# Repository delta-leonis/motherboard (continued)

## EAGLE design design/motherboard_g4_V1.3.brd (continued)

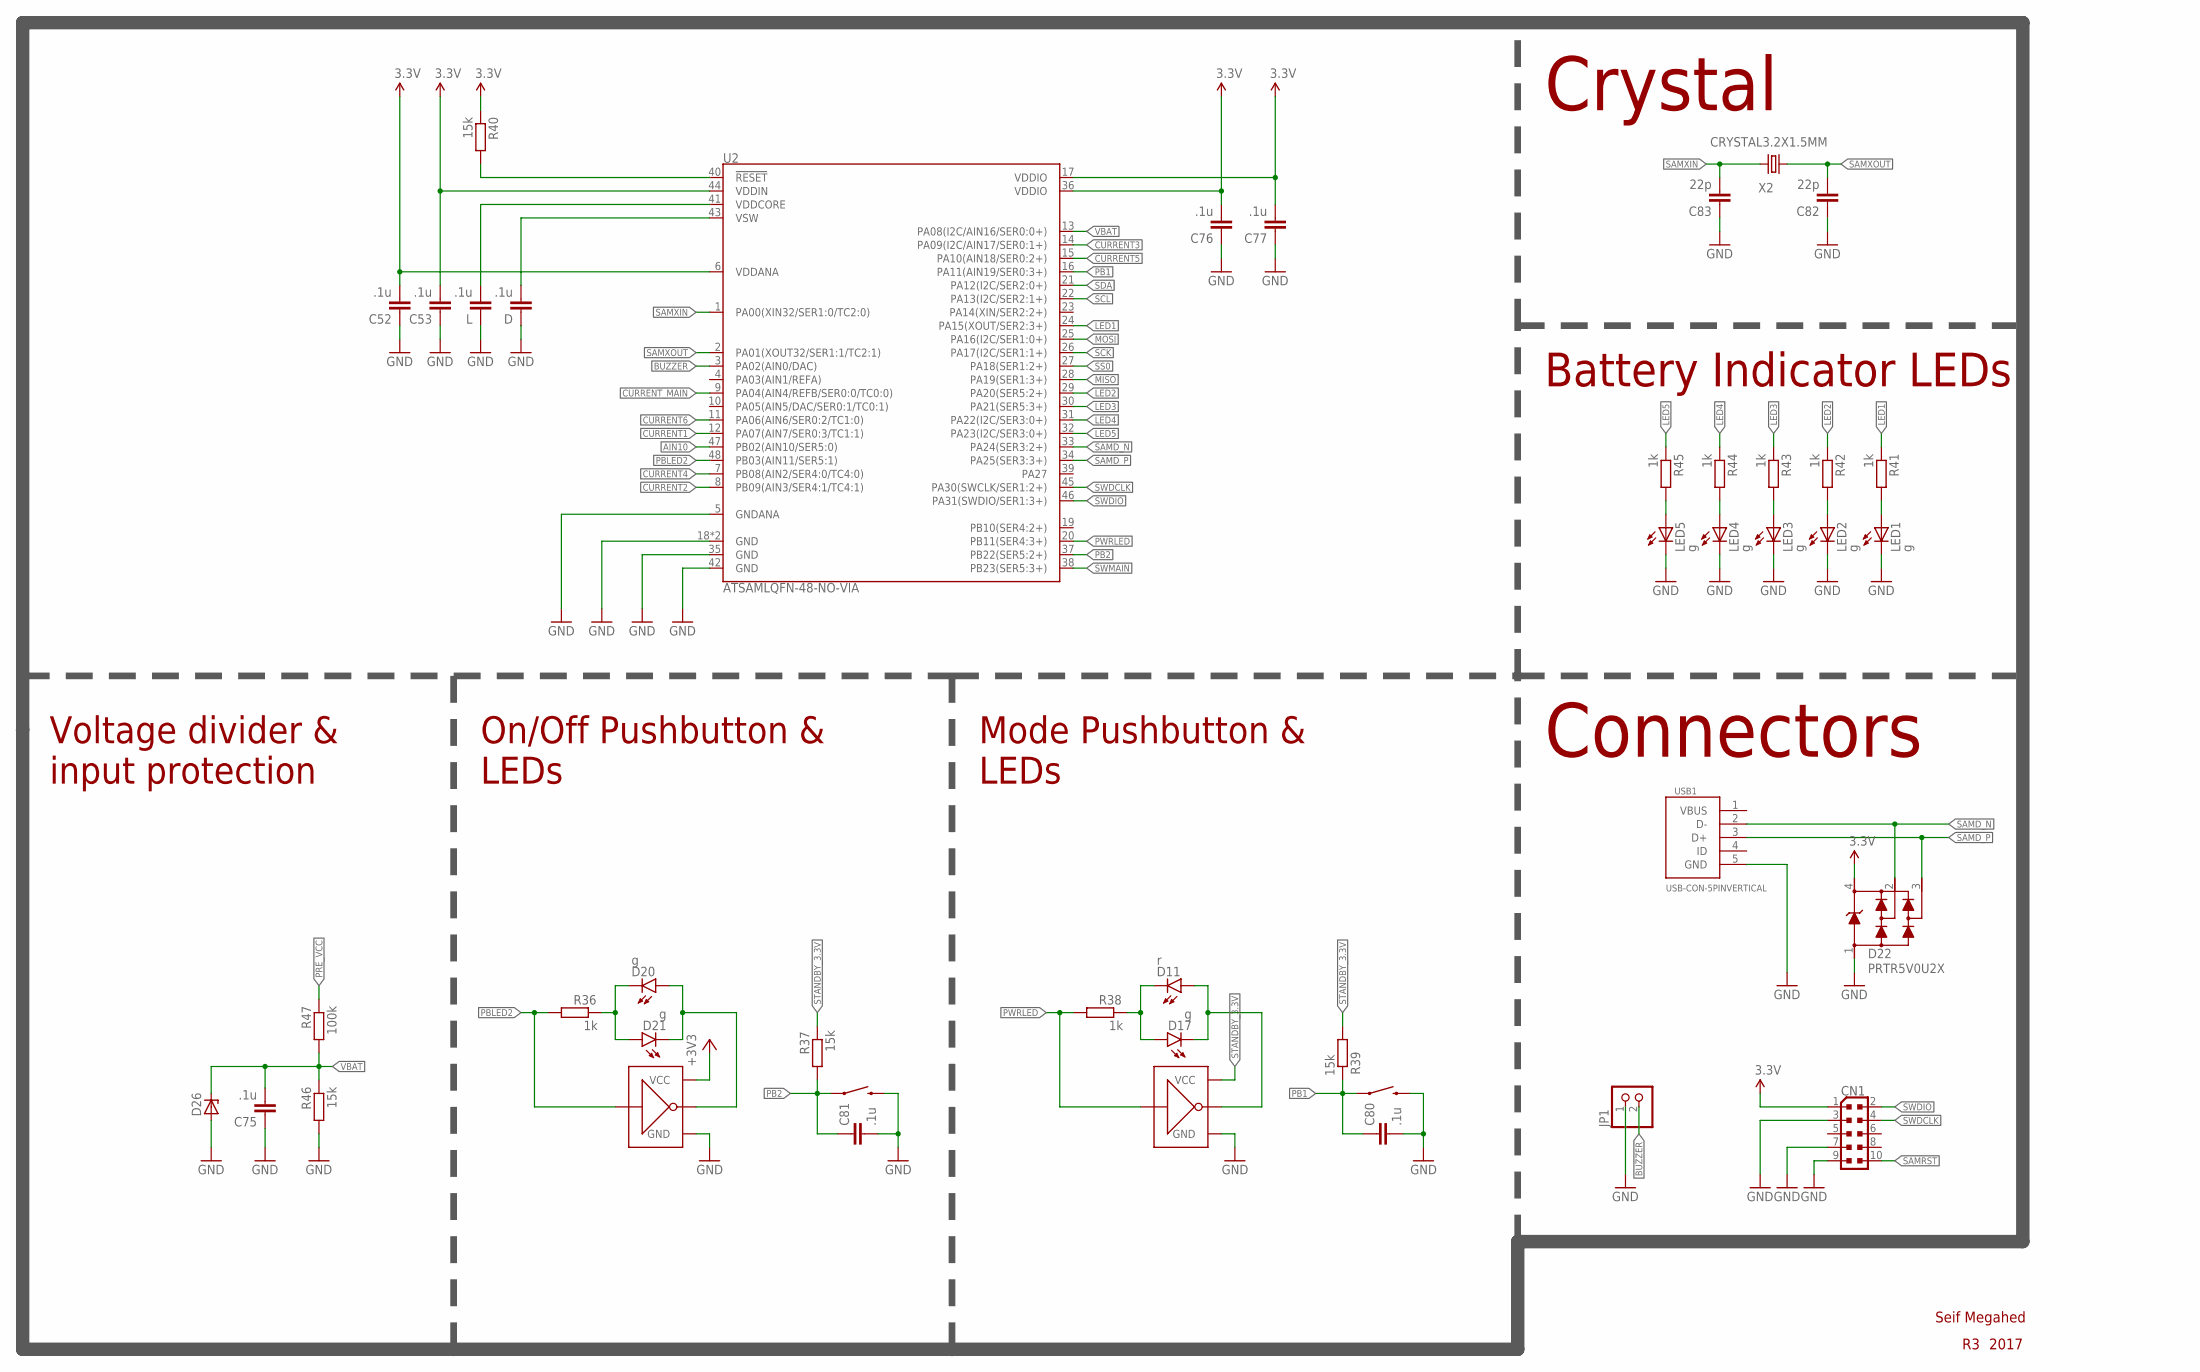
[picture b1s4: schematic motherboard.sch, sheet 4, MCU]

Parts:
C52, C53, C75, C76, C77, C80, C81: .1u; CAP_0603
C82, C83: 22p; CAP_0603
CN1: SWD_0171_PH127-205DF055G00AROUND-PADS; SWD_PINHEAD_2X05_127
D: .1u; CAP_0603
D11: r; LED-0603
D17, D20, D21: g; LED-0603
D22: PRTR5V0U2X; SOT143B
D26: http://nl.farnell.com/diodes-inc/dz23c3v3-7-f/dio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; SOT23
JP1: PINHD-1X2; 1X02
L: .1u; CAP_0603
LED1, LED2, LED3, LED4, LED5: g; CHIP-LED0603
NOT1, NOT2: NOT_GATE7404_SOT23-5; SOT23-5
R36, R38: 1k; 0603
R37, R39: 15k; 0603
R40, R46: 15k; RES_0603
R41, R42, R43, R44, R45: 1k; RES_0603
R47: 100k; RES_0603
U2: ATSAMLQFN-48-NO-VIA; QFN-48-NO-VIAS
U$31, U$32: http://nl.mouser.com/ProductDetail/Omron-Electron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; TACT12X12
USB1: USB-CON-5PINVERTICAL; USB-MICRO-3131-V
X2: CRYSTAL3.2X1.5MM; CRYSTAL-SMD-3.2X1.5MM

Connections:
+3V3: NOT2.5 (VCC); also elsewhere on the board
AIN10: U2.47 (PB02(AIN10/SER5:0))
BUZZER: JP1.2, U2.3 (PA02(AIN0/DAC))
CURRENT1: U2.12 (PA07(AIN7/SER0:3/TC1:1)); also elsewhere on the board
CURRENT2: U2.8 (PB09(AIN3/SER4:1/TC4:1)); also elsewhere on the board
CURRENT3: U2.14 (PA09(I2C/AIN17/SER0:1+)); also elsewhere on the board
CURRENT4: U2.7 (PB08(AIN2/SER4:0/TC4:0)); also elsewhere on the board
CURRENT5: U2.15 (PA10(AIN18/SER0:2+)); also elsewhere on the board
CURRENT6: U2.11 (PA06(AIN6/SER0:2/TC1:0)); also elsewhere on the board
CURRENT_MAIN: U2.9 (PA04(AIN4/REFB/SER0:0/TC0:0)); also elsewhere on the board
D: D.2, U2.43 (VSW)
GND: C52.1, C53.1, C75.1, C76.1, C77.1, C80.2, C81.2, C82.1, C83.1, CN1.3, CN1.7, CN1.9, D.1, D22.1, D26.1 (A), JP1.1, L.1, LED1.C, LED2.C, LED3.C, LED4.C, LED5.C, NOT1.3 (GND), NOT2.3 (GND), R46.2, U2.5 (GNDANA), U2.18 (GND), U2.35 (GND), U2.42 (GND), U2.EP (GND), U$31.3 (2), U$31.4 (2), U$32.3 (2), U$32.4 (2), USB1.5 (GND); also elsewhere on the board
L: L.2, U2.41 (VDDCORE)
LED1: R41.1, U2.24 (PA15(XOUT/SER2:3+))
LED2: R42.1, U2.29 (PA20(SER5:2+))
LED3: R43.1, U2.30 (PA21(SER5:3+))
LED4: R44.1, U2.31 (PA22(I2C/SER3:0+))
LED5: R45.1, U2.32 (PA23(I2C/SER3:0+))
MISO: U2.28 (PA19(SER1:3+)); also elsewhere on the board
MOSI: U2.25 (PA16(I2C/SER1:0+)); also elsewhere on the board
unnamed: D20.C, D21.A, R36.P$1 (1)
unnamed: D11.C, D17.A, R38.P$1 (1)
unnamed: D11.A, D17.C, NOT1.4 (Y)
unnamed: D20.A, D21.C, NOT2.4 (Y)
unnamed: LED5.A, R45.2
unnamed: LED4.A, R44.2
unnamed: LED3.A, R43.2
unnamed: LED2.A, R42.2
unnamed: LED1.A, R41.2
PB1: C80.1, R39.P$1 (1), U2.16 (PA11(AIN19/SER0:3+)), U$31.1, U$31.2 (1)
PB2: C81.1, R37.P$2 (2), U2.37 (PB22(SER5:2+)), U$32.1, U$32.2 (1)
PBLED2: NOT2.2 (A), R36.P$2 (2), U2.48 (PB03(AIN11/SER5:1))
PRE_VCC: R47.1; also elsewhere on the board
PWRLED: NOT1.2 (A), R38.P$2 (2), U2.20 (PB11(SER4:3+))
SAMD_N: D22.2, U2.33 (PA24(SER3:2+)), USB1.2 (D-)
SAMD_P: D22.3, U2.34 (PA25(SER3:3+)), USB1.3 (D+)
SAMRST: CN1.10, R40.2, U2.40 (!RESET!)
SAMXIN: C83.2, U2.1 (PA00(XIN32/SER1:0/TC2:0)), X2.P$2 (2)
SAMXOUT: C82.2, U2.2 (PA01(XOUT32/SER1:1/TC2:1)), X2.P$1 (1)
SCK: U2.26 (PA17(I2C/SER1:1+)); also elsewhere on the board
SCL: U2.22 (PA13(I2C/SER2:1+)); also elsewhere on the board
SDA: U2.21 (PA12(I2C/SER2:0+)); also elsewhere on the board
SS0: U2.27 (PA18(SER1:2+)); also elsewhere on the board
STANDBY_3.3V: C52.2, C53.2, C76.2, C77.2, CN1.1, D22.4, NOT1.5 (VCC), R37.P$1 (1), R39.P$2 (2), R40.1, U2.6 (VDDANA), U2.17 (VDDIO), U2.36 (VDDIO), U2.44 (VDDIN); also elsewhere on the board
SWDCLK: CN1.4, U2.45 (PA30(SWCLK/SER1:2+))
SWDIO: CN1.2, U2.46 (PA31(SWDIO/SER1:3+))
SWMAIN: U2.38 (PB23(SER5:3+)); also elsewhere on the board
VBAT: C75.2, D26.3 (C), R46.1, R47.2, U2.13 (PA08(I2C/AIN16/SER0:0+))
VBUS: USB1.1 (VBUS)

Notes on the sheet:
Connectors
Battery Indicator LEDs
Crystal
Voltage divider & input protection
On/Off Pushbutton & LEDs
Mode Pushbutton & LEDs
Seif Megahed
2017

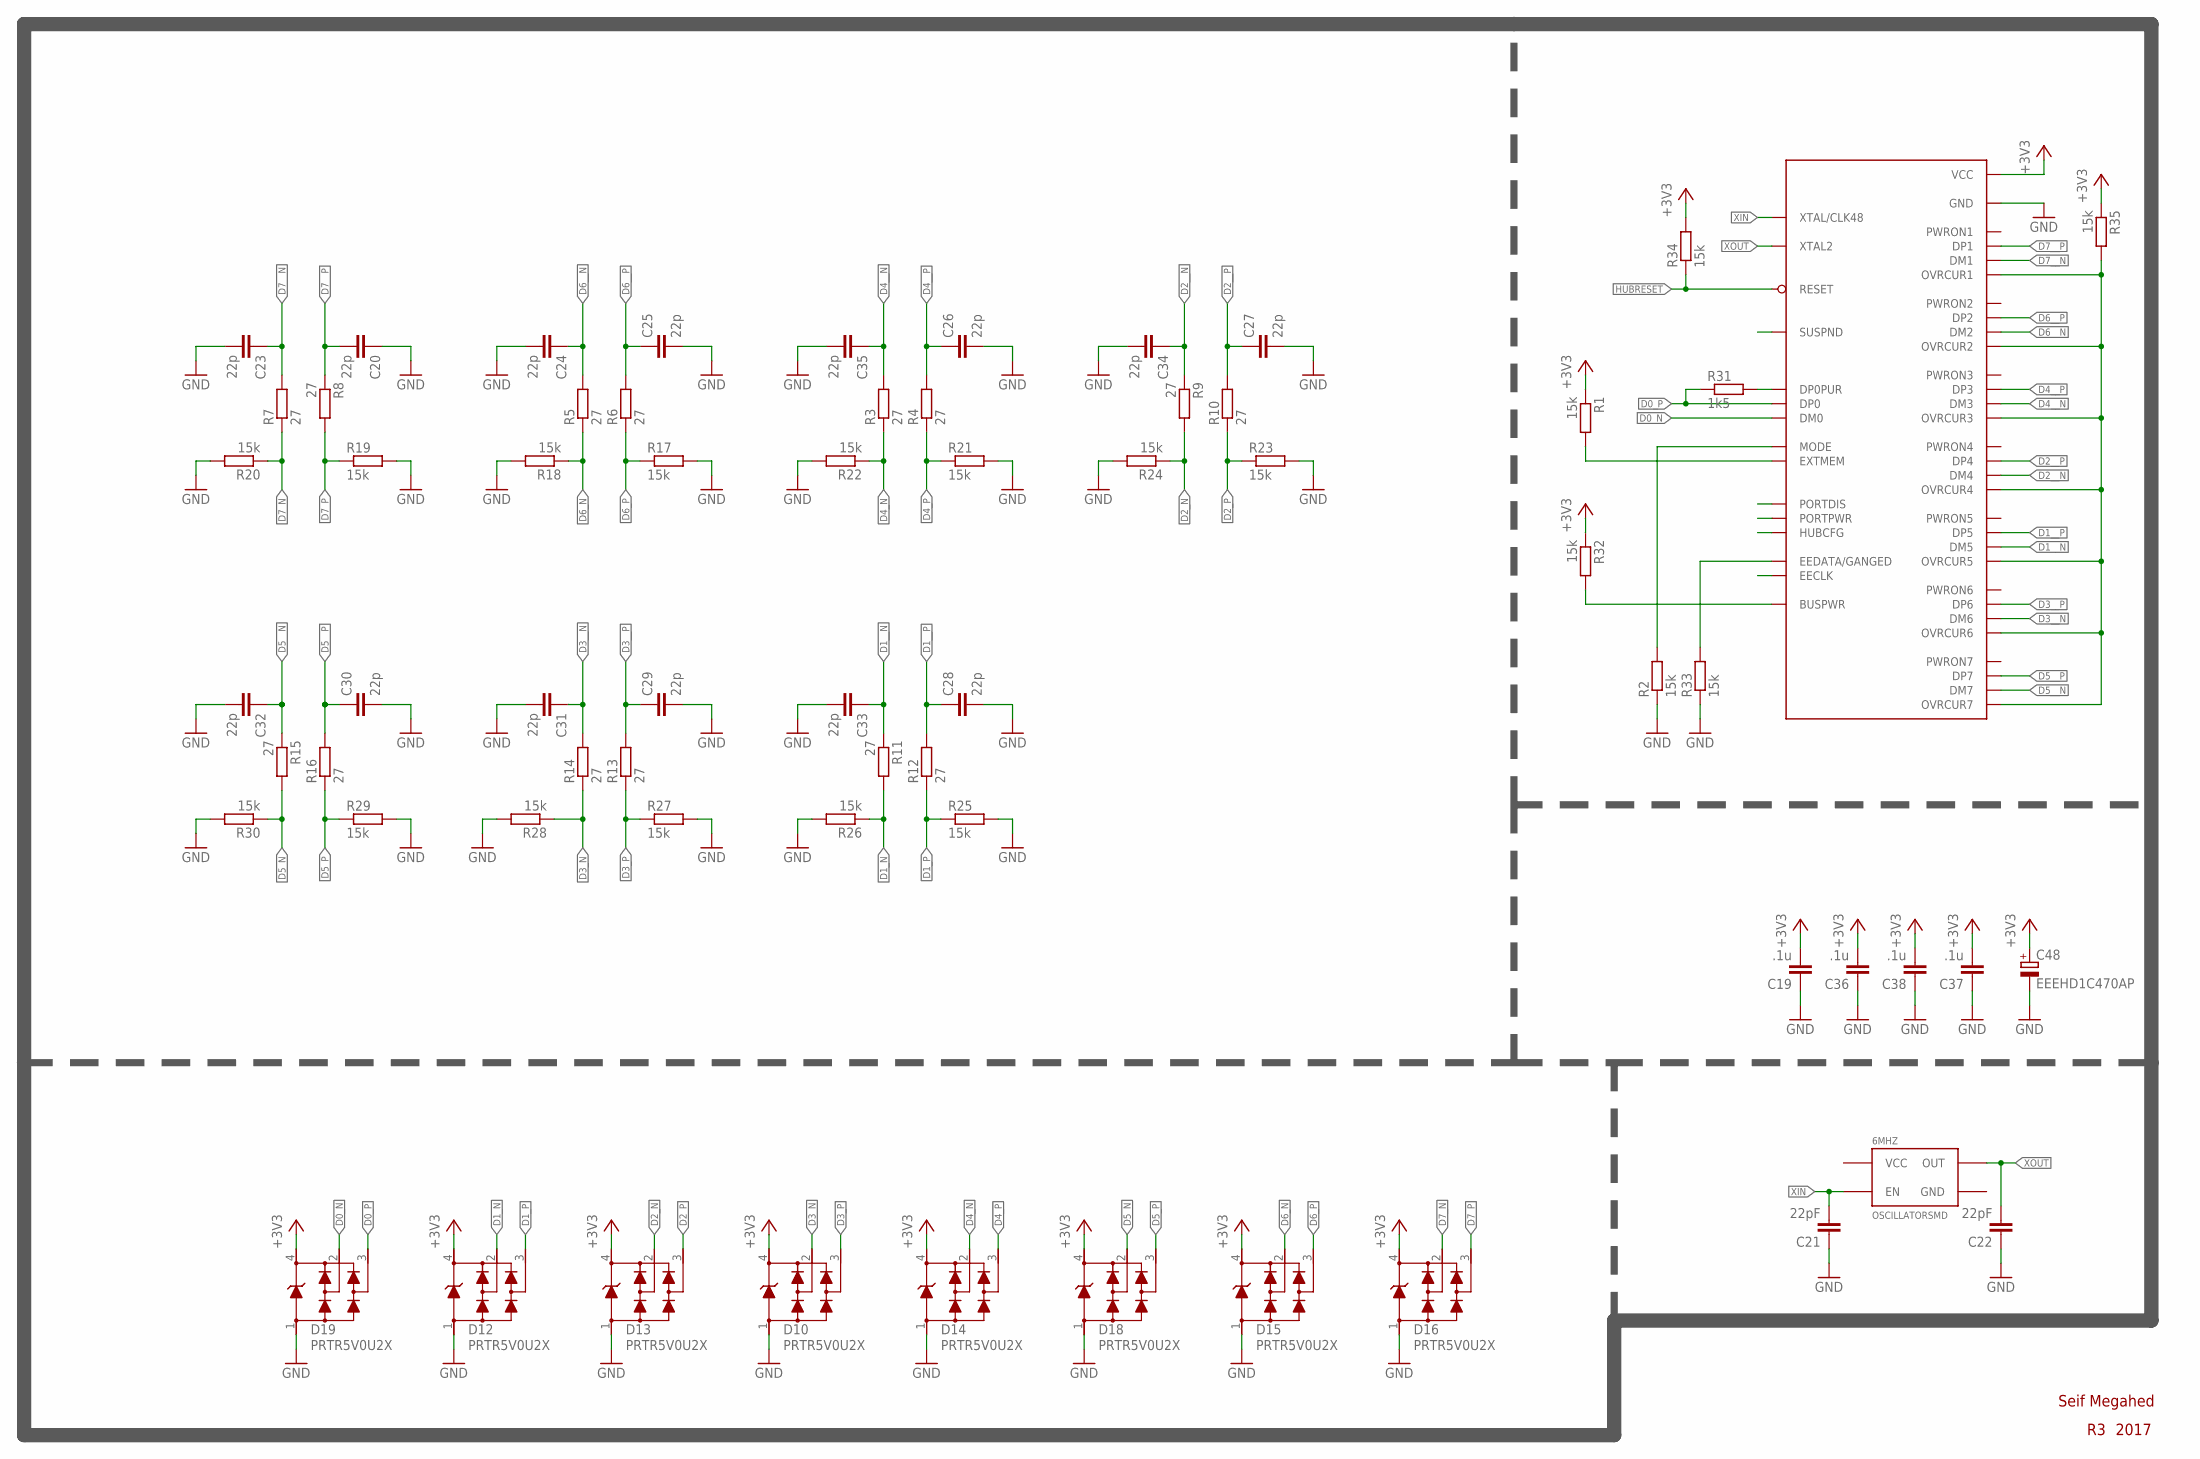
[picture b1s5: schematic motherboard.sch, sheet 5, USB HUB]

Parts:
6MHZ: OSCILLATORSMD; CRYSTAL-SMD-7X5
C19, C36, C37, C38: .1u; CAP_0603
C20, C23, C24, C25, C26, C27, C28, C29, C30, C31, C32, C33, C34, C35: 22p; CAP_0603
C21, C22: 22pF; CAP_0603
C48: EEEHD1C470AP; PANASONIC_C
D10, D12, D13, D14, D15, D16, D18, D19: PRTR5V0U2X; SOT143B
R1, R2, R17, R18, R19, R20, R21, R22, R23, R24, R25, R26, R27, R28, R29, R30, R32, R33, R34, R35: 15k; RES_0603
R3, R4, R5, R6, R7, R8, R9, R10, R11, R12, R13, R14, R15, R16: 27; RES_0603
R31: 1k5; RES_0603
U1: TUSB2077ALQFP-48; LQFP-48

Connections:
+3V3: C19.2, C36.2, C37.2, C38.2, C48.+, D10.4, D12.4, D13.4, D14.4, D15.4, D16.4, D18.4, D19.4, R1.1, R32.1, R34.2, R35.1, U1.9 (VCC), U1.46 (VCC); also elsewhere on the board
BUSPWR: R32.2, U1.10 (BUSPWR)
D0_N: D19.2, U1.4 (DM0); also elsewhere on the board
D0_P: D19.3, R31.1, U1.3 (DP0); also elsewhere on the board
D1_N: D12.2, R11.2, R26.1; also elsewhere on the board
D1_P: D12.3, R12.1, R25.1; also elsewhere on the board
D1__N: C33.1, R11.1, U1.30 (DM5)
D1__P: C28.1, R12.2, U1.31 (DP5)
D2_N: D13.2, R9.2, R24.1; also elsewhere on the board
D2_P: D13.3, R10.1, R23.1; also elsewhere on the board
D2__N: C34.1, R9.1, U1.26 (DM4)
D2__P: C27.1, R10.2, U1.27 (DP4)
D3_N: D10.2, R14.1, R28.1; also elsewhere on the board
D3_P: D10.3, R13.1, R27.1; also elsewhere on the board
D3__N: C31.1, R14.2, U1.34 (DM6)
D3__P: C29.1, R13.2, U1.35 (DP6)
D4_N: D14.2, R3.1, R22.1; also elsewhere on the board
D4_P: D14.3, R4.1, R21.1; also elsewhere on the board
D4__N: C35.1, R3.2, U1.21 (DM3)
D4__P: C26.1, R4.2, U1.22 (DP3)
D5_N: D18.2, R15.2, R30.1; also elsewhere on the board
D5_P: D18.3, R16.1, R29.1; also elsewhere on the board
D5__N: C32.1, R15.1, U1.38 (DM7)
D5__P: C30.1, R16.2, U1.39 (DP7)
D6_N: D15.2, R5.1, R18.1; also elsewhere on the board
D6_P: D15.3, R6.1, R17.1; also elsewhere on the board
D6__N: C24.1, R5.2, U1.17 (DM2)
D6__P: C25.1, R6.2, U1.18 (DP2)
D7_N: D16.2, R7.1, R20.1; also elsewhere on the board
D7_P: D16.3, R8.2, R19.1; also elsewhere on the board
D7__N: C23.1, R7.2, U1.13 (DM1)
D7__P: C20.2, R8.1, U1.14 (DP1)
DPUR: R31.2, U1.2 (DP0PUR)
EEDATA: R33.2, U1.8 (EEDATA/GANGED)
EXTMEM: R1.2, U1.47 (EXTMEM)
GND: C19.1, C20.1, C21.1, C22.1, C23.2, C24.2, C25.2, C26.2, C27.2, C28.2, C29.2, C30.2, C31.2, C32.2, C33.2, C34.2, C35.2, C36.1, C37.1, C38.1, C48.-, D10.1, D12.1, D13.1, D14.1, D15.1, D16.1, D18.1, D19.1, R2.1, R17.2, R18.2, R19.2, R20.2, R21.2, R22.2, R23.2, R24.2, R25.2, R26.2, R27.2, R28.2, R29.2, R30.2, R33.1, U1.5 (GND), U1.24 (GND), U1.43 (GND); also elsewhere on the board
HUBRESET: R34.1, U1.6 (RESET)
MODE: R2.2, U1.48 (MODE)
OC: R35.2, U1.12 (OVRCUR1), U1.16 (OVRCUR2), U1.20 (OVRCUR3), U1.25 (OVRCUR4), U1.29 (OVRCUR5), U1.33 (OVRCUR6), U1.37 (OVRCUR7)
XIN: 6MHZ.P$1 (EN), C21.2, U1.45 (XTAL/CLK48)
XOUT: 6MHZ.P$3 (OUT), C22.2, U1.44 (XTAL2)

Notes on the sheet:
Seif Megahed
2017

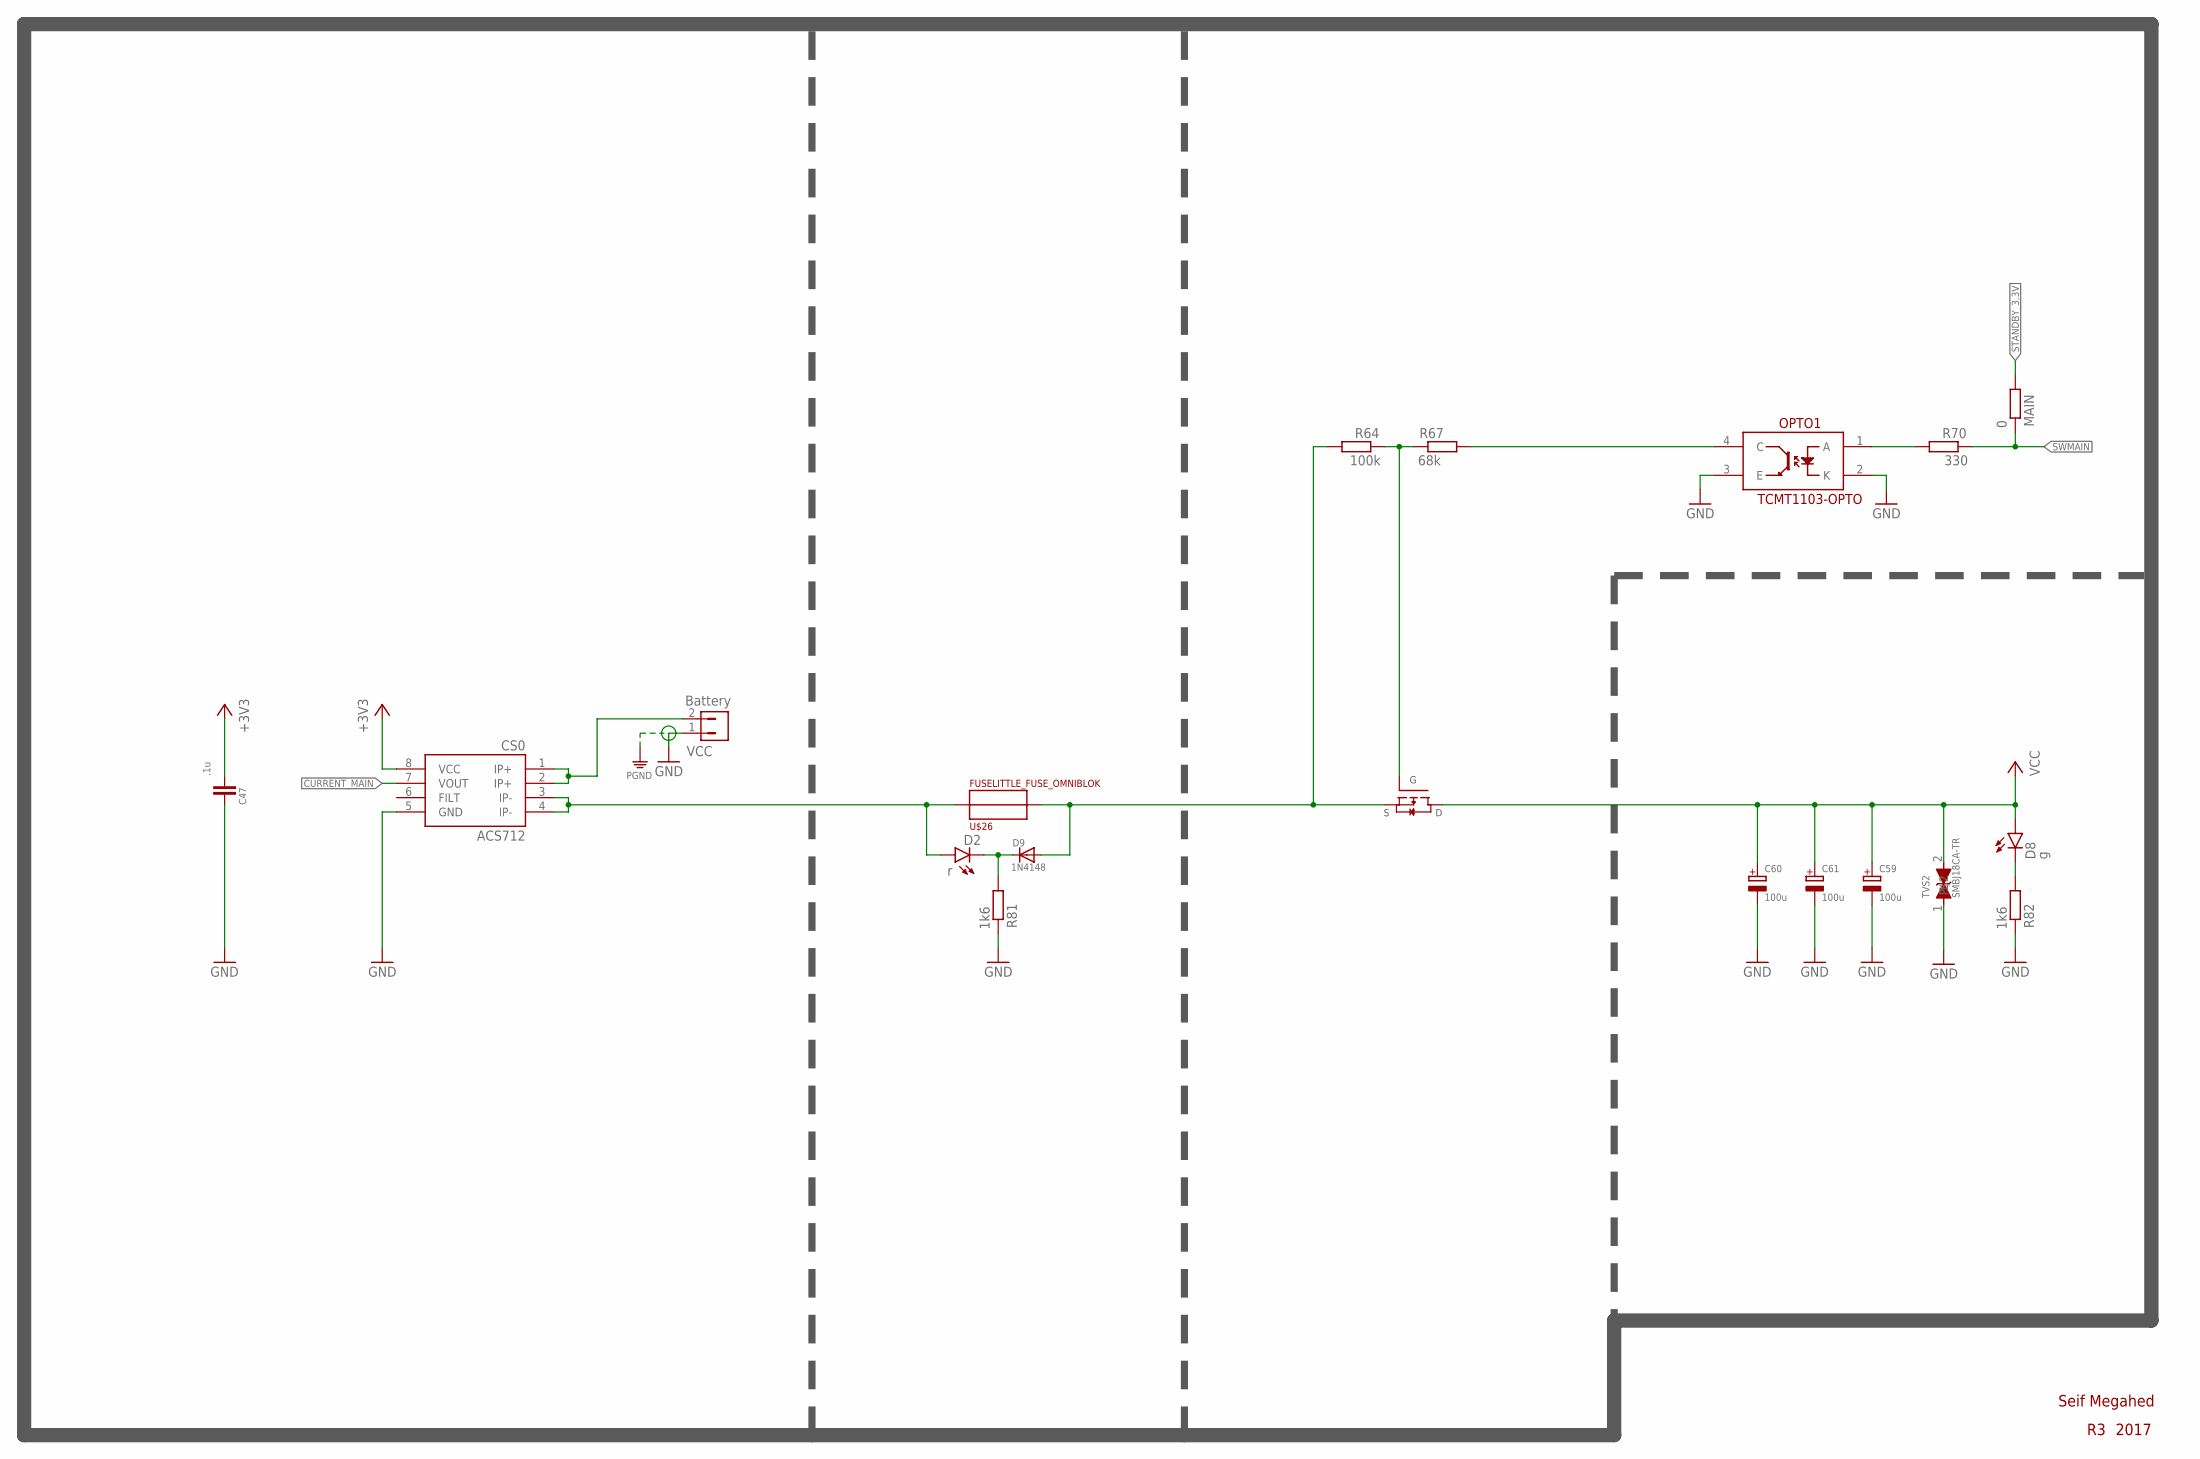
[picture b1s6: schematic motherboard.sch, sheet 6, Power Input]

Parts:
C47: .1u; 0603
C59, C60, C61: 100u; AE_CAP_D
CS0: ACS712; SO08
D2: r; LED-0603
D8: g; LED-0603
D9: 1N4148; SOD-80
MAIN: 0; 0603
OPTO1: TCMT1103-OPTO; SSOP-4
R64: 100k; 0603
R67: 68k; 0603
R70: 330; 0603
R81, R82: 1k6; 0603
TVS2: SMBJ18CA-TR; IPC_7531
U$26: FUSELITTLE_FUSE_OMNIBLOK; OMNI_BLOK
U$30: MOSFETSIR401DP; POWERPAK_SO-8
VCC: Battery; MOLEX_2_RIGHT

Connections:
+3V3: C47.P$2 (2), CS0.8 (VCC); also elsewhere on the board
BAT: CS0.1 (IP+), CS0.2 (IP+), VCC.2
CURRENT_MAIN: CS0.7 (VOUT); also elsewhere on the board
GND: C47.P$1 (1), C59.-, C60.-, C61.-, CS0.5 (GND), OPTO1.2 (K), OPTO1.3 (E), R81.P$1 (1), R82.P$1 (1), TVS2.1, VCC.1; also elsewhere on the board
MOSFET_GATE: OPTO1.4 (C), R67.P$2 (2)
unnamed: R64.P$1 (1), R67.P$1 (1), U$30.4 (G)
unnamed: OPTO1.1 (A), R70.P$2 (2)
unnamed: D2.C, D9.2 (C), R81.P$2 (2)
unnamed: D8.C, R82.P$2 (2)
PRE_VCC: CS0.3 (IP-), CS0.4 (IP-), D2.A, U$26.P$1; also elsewhere on the board
S: D9.1 (A), R64.P$2 (2), U$26.P$2, U$30.1 (S), U$30.2 (S), U$30.3 (S)
STANDBY_3.3V: MAIN.P$2 (2); also elsewhere on the board
SWMAIN: MAIN.P$1 (1), R70.P$1 (1); also elsewhere on the board
VCC: C59.+, C60.+, C61.+, D8.A, TVS2.2, U$30.5 (D), U$30.6 (D), U$30.7 (D), U$30.8 (D), U$30.EP (D); also elsewhere on the board

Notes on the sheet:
Seif Megahed
2017

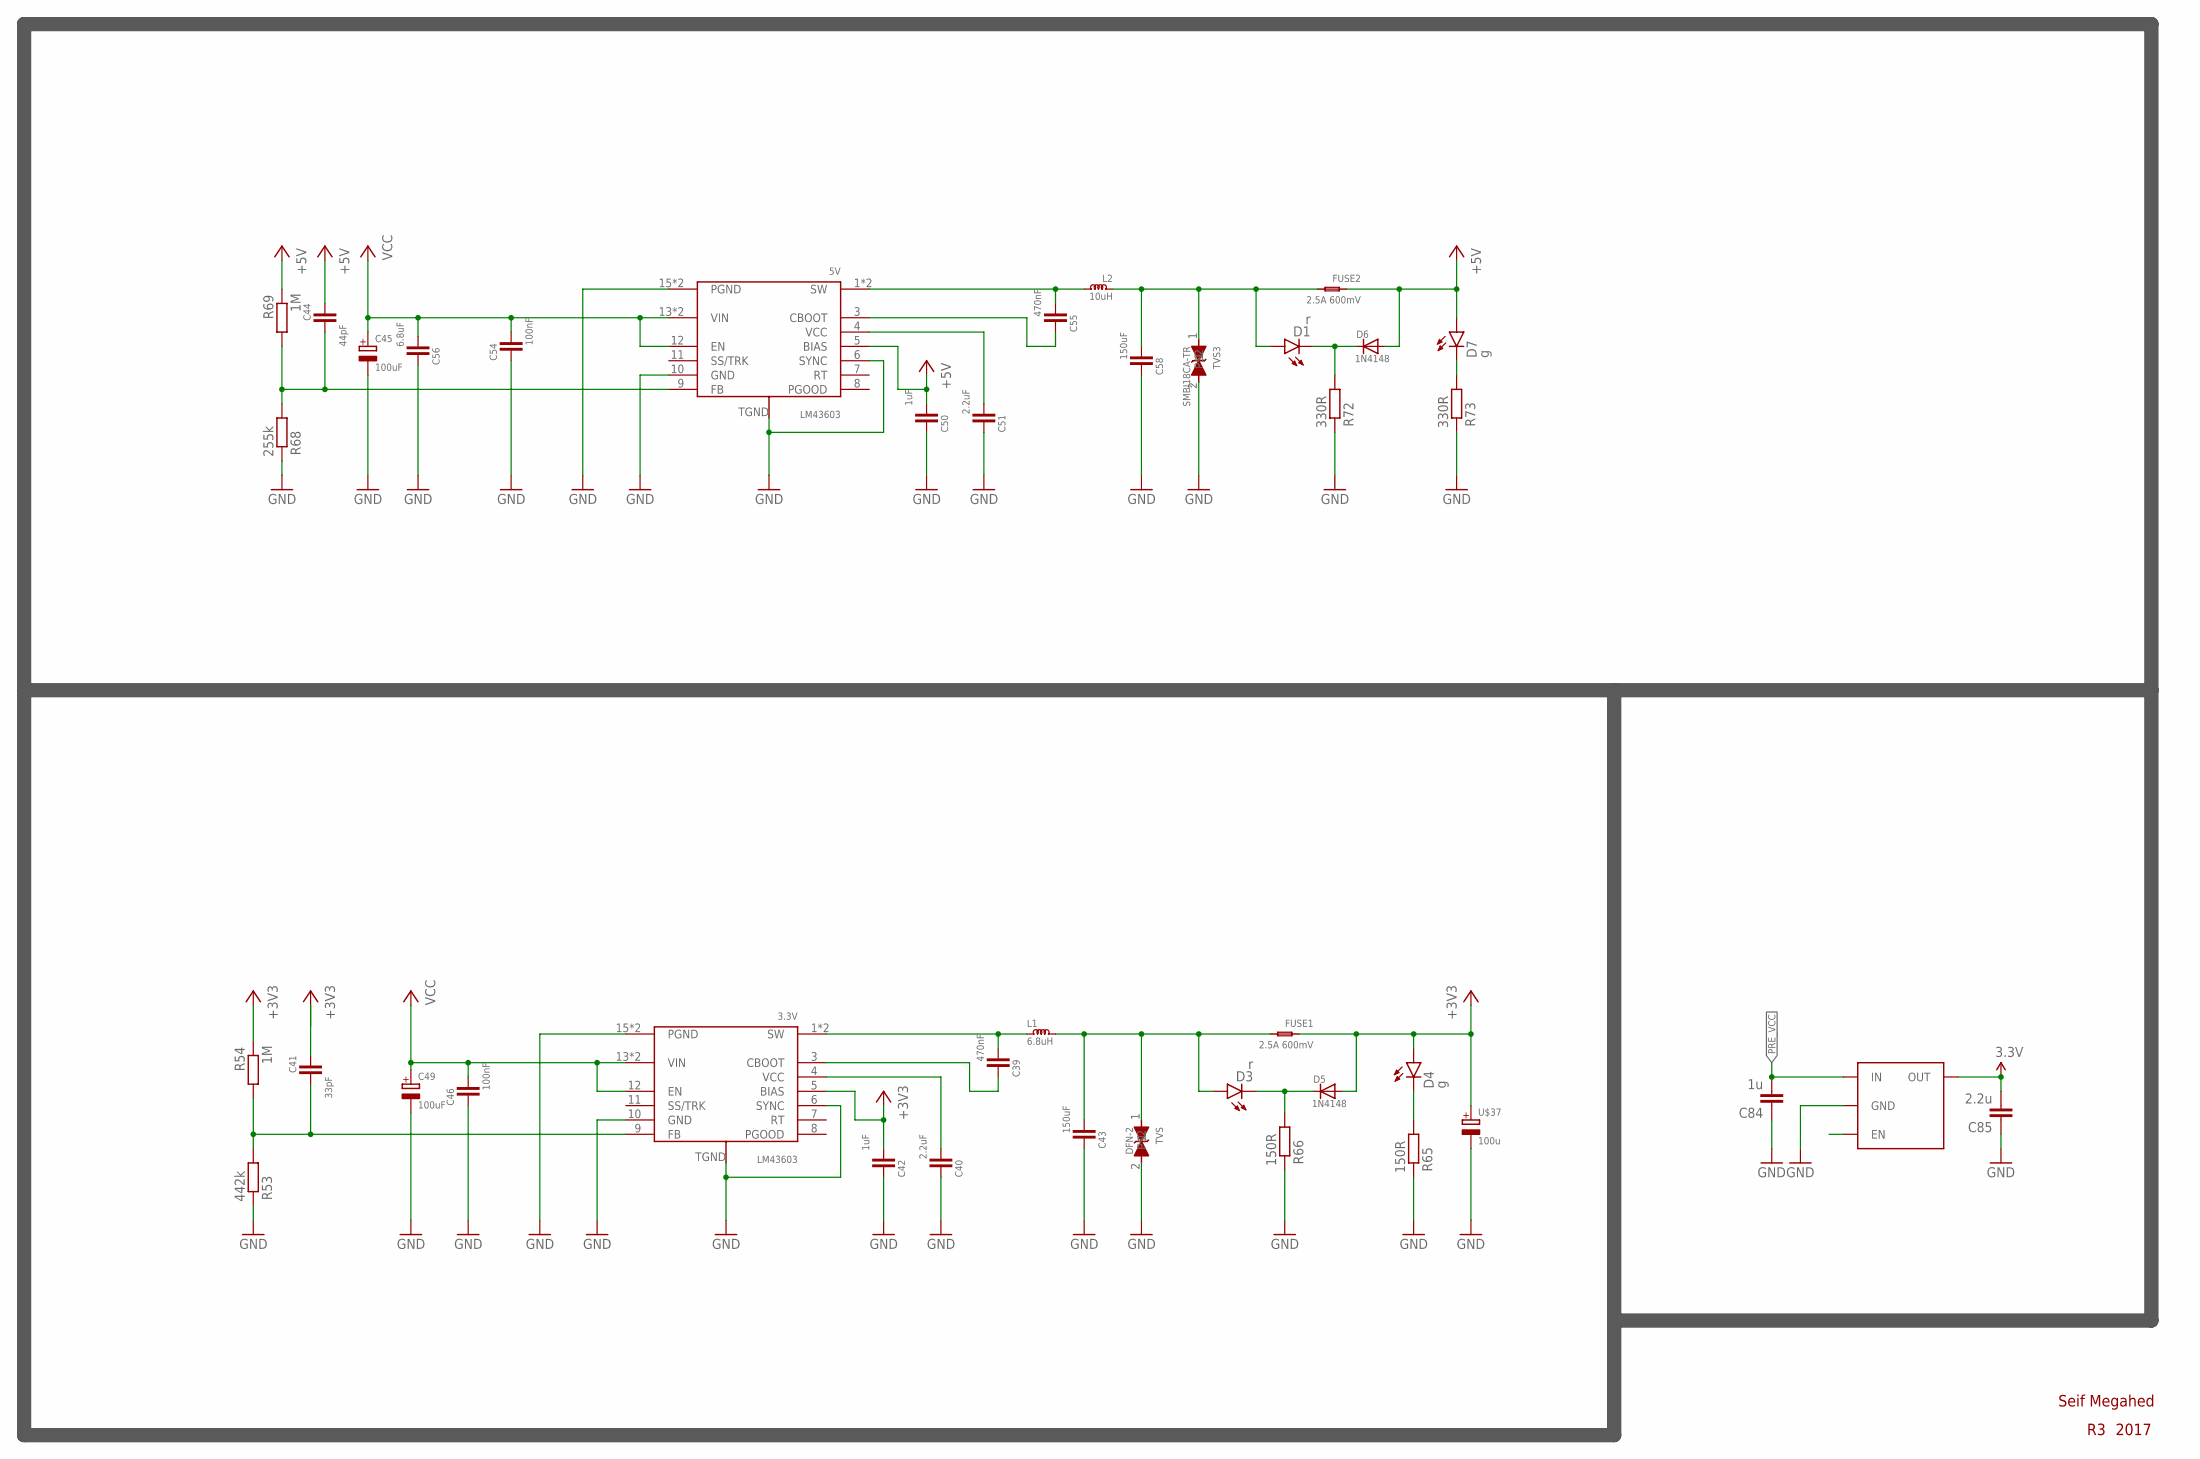
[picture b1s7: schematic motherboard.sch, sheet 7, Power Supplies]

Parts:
3: http://nl.farnell.com/texas-instruments/tps709b33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; SOT23-5
3.3V, 5V: LM43603; HTSSOP16
C39, C55: 470nF; 0603
C40, C51: 2.2uF; 0603
C41: 33pF; 0603
C42, C50: 1uF; 0603
C43, C58: 150uF; 1206
C44: 44pF; 0603
C45, C49: 100uF; AE_CAP_D
C46, C54: 100nF; 0603
C56: 6.8uF; 0805
C84: 1u; CAP_0603
C85: 2.2u; CAP_0603
D1, D3: r; LED-0603
D4, D7: g; LED-0603
D5, D6: 1N4148; SOD-80
FUSE1, FUSE2: 2.5A 600mV; 1812
L1: 6.8uH; WE-PD2SR/7850
L2: 10uH; WE-PD2/1054
R53: 442k; 0603
R54, R69: 1M; 0603
R65, R66: 150R; 0603
R68: 255k; 0603
R72, R73: 330R; 0603
TVS: DFN-2
TVS3: SMBJ18CA-TR; IPC_7531
U$37: 100u; AE_CAP_D

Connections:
+3V1: C43.P$2 (2), D3.A, FUSE1.2, L1.2, TVS.1
+3V3: 3.3V.5 (BIAS), C41.P$1 (1), C42.P$2 (2), D4.A, D5.1 (A), FUSE1.1, R54.P$1 (1), U$37.+; also elsewhere on the board
+5V: 5V.5 (BIAS), C44.P$1 (1), C50.P$2 (2), D6.1 (A), D7.A, FUSE2.1, R69.P$1 (1); also elsewhere on the board
EN: 3.3 (EN)
GND: 3.2 (GND), 3.3V.6 (SYNC), 3.3V.10 (GND), 3.3V.15 (PGND), 3.3V.16 (PGND), 3.3V.TGND (AGND), 5V.6 (SYNC), 5V.10 (GND), 5V.15 (PGND), 5V.16 (PGND), 5V.TGND (AGND), C40.P$1 (1), C42.P$1 (1), C43.P$1 (1), C45.-, C46.P$1 (1), C49.-, C50.P$1 (1), C51.P$1 (1), C54.P$1 (1), C56.1, C58.P$1 (1), C84.1, C85.1, R53.P$1 (1), R65.P$1 (1), R66.P$1 (1), R68.P$1 (1), R72.P$1 (1), R73.P$1 (1), TVS.2, TVS3.2, U$37.-; also elsewhere on the board
unnamed: 3.3V.3 (CBOOT), C39.P$1 (1)
unnamed: 3.3V.4 (VCC), C40.P$2 (2)
unnamed: 3.3V.9 (FB), C41.P$2 (2), R53.P$2 (2), R54.P$2 (2)
unnamed: 3.3V.1 (SW), 3.3V.2 (SW), C39.P$2 (2), L1.1
unnamed: D3.C, D5.2 (C), R66.P$2 (2)
unnamed: 5V.3 (CBOOT), C55.P$1 (1)
unnamed: 5V.4 (VCC), C51.P$2 (2)
unnamed: 5V.9 (FB), C44.P$2 (2), R68.P$2 (2), R69.P$2 (2)
unnamed: 5V.1 (SW), 5V.2 (SW), C55.P$2 (2), L2.P$2 (2)
unnamed: D1.C, D6.2 (C), R72.P$2 (2)
unnamed: D4.C, R65.P$2 (2)
unnamed: D7.C, R73.P$2 (2)
PRE_VCC: 3.1 (IN), C84.2; also elsewhere on the board
STANDBY_3.3V: 3.5 (OUT), C85.2; also elsewhere on the board
VCC: 3.3V.12 (EN), 3.3V.13 (VIN), 3.3V.14 (VIN), 5V.12 (EN), 5V.13 (VIN), 5V.14 (VIN), C45.+, C46.P$2 (2), C49.+, C54.P$2 (2), C56.2; also elsewhere on the board
VCC3: C58.P$2 (2), D1.A, FUSE2.2, L2.P$1 (1), TVS3.1

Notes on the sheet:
Seif Megahed
2017
